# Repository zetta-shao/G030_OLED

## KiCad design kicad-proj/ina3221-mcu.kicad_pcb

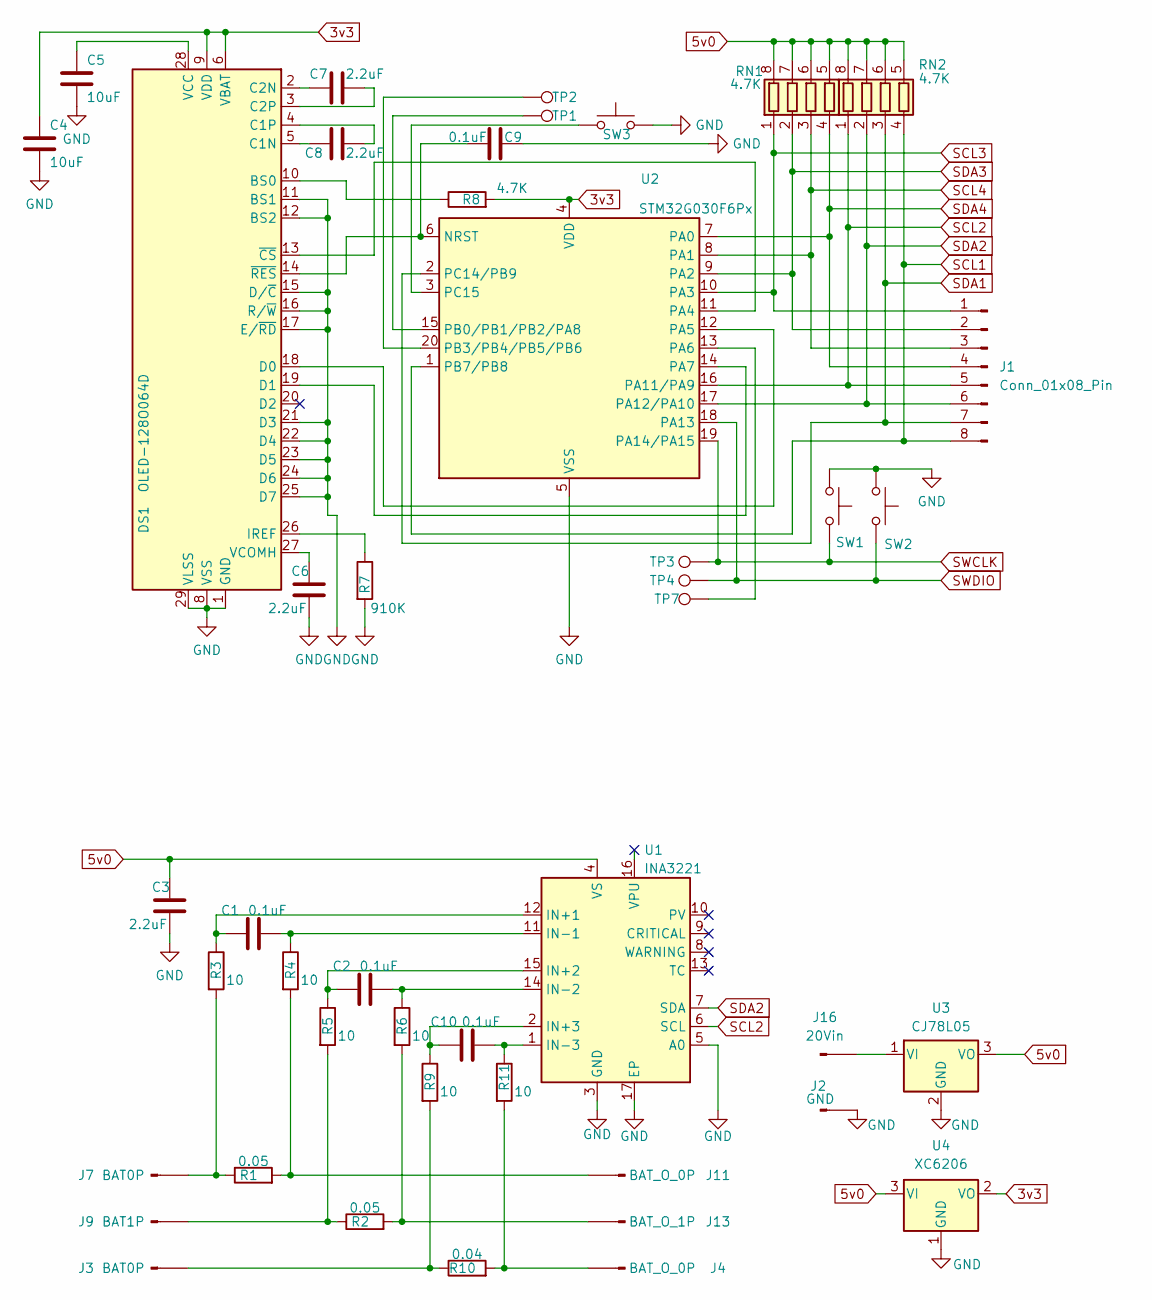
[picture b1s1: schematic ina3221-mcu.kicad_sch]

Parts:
C1, C2, C9, C10: 0.1uF; C_0603_1608Metric_Pad1.08x0.95mm_HandSolder
C3, C6, C7, C8: 2.2uF; C_0603_1608Metric_Pad1.08x0.95mm_HandSolder
C4, C5: 10uF; C_0603_1608Metric_Pad1.08x0.95mm_HandSolder
DS1: OLED-128O064D
J1: Conn_01x08_Pin; PinHeader_1x08_P1.00mm_Vertical
J2: GND; SolderWire-0.127sqmm_1x01_D0.48mm_OD1mm
J3, J7: BAT0P; SolderWire-0.127sqmm_1x01_D0.48mm_OD1mm
J4, J11: BAT_O_0P; SolderWire-0.127sqmm_1x01_D0.48mm_OD1mm
J9: BAT1P; SolderWire-0.127sqmm_1x01_D0.48mm_OD1mm
J13: BAT_O_1P; SolderWire-0.127sqmm_1x01_D0.48mm_OD1mm
J16: 20Vin; SolderWire-0.127sqmm_1x01_D0.48mm_OD1mm
R1, R2: 0.05; R_1206_3216Metric_Pad1.30x1.75mm_HandSolder
R3, R4, R5, R6, R9, R11: 10; R_0603_1608Metric_Pad0.98x0.95mm_HandSolder
R7: 910K; R_0603_1608Metric_Pad0.98x0.95mm_HandSolder
R8: 4.7K; R_0603_1608Metric_Pad0.98x0.95mm_HandSolder
R10: 0.04; R_1206_3216Metric_Pad1.30x1.75mm_HandSolder
RN1, RN2: 4.7K; R_Array_Concave_4x0603
SW1, SW2, SW3: SW_Push; SW_SPST_TL3305A
TP1, TP2: TestPoint; TestPoint_Pad_1.0x1.0mm
TP3: SWCLK; TestPoint_Pad_2.0x2.0mm
TP4: SWDIO; TestPoint_Pad_2.0x2.0mm
TP7: TestPoint_Pad_1.0x1.0mm
U1: INA3221; QFN-16-1EP_4x4mm_P0.65mm_EP2.1x2.1mm
U2: STM32G030F6Px; TSSOP-20_4.4x6.5mm_P0.65mm
U3: CJ78L05; SOT-89-3
U4: XC6206; SOT-23

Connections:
3v3: C4.1, DS1.6 (VBAT), DS1.9 (VDD), R8.2, U2.4 (VDD), U4.2 (VO)
5v0: C3.1, RN1.5 (R4.2), RN1.6 (R3.2), RN1.7 (R2.2), RN1.8 (R1.2), RN2.5 (R4.2), RN2.6 (R3.2), RN2.7 (R2.2), RN2.8 (R1.2), U1.4 (VS), U3.3 (VO), U4.3 (VI)
GND: C3.2, C4.2, C5.2, C6.2, C9.1, DS1.1 (GND), DS1.8 (VSS), DS1.11 (BS1), DS1.12 (BS2), DS1.15 (D/~C), DS1.16 (R/~W), DS1.17 (E/~RD), DS1.21 (D3), DS1.22 (D4), DS1.23 (D5), DS1.24 (D6), DS1.25 (D7), DS1.29 (VLSS), DS1.30 (GND), J2.1, R7.2, SW1.1, SW2.1, SW3.2, U1.3 (GND), U1.5 (A0), U1.17 (EP), U2.5 (VSS), U3.2 (GND), U4.1 (GND)
unnamed: DS1.10 (BS0), R8.1
unnamed: C8.1, DS1.5 (C1N)
unnamed: C8.2, DS1.4 (C1P)
unnamed: C7.1, DS1.2 (C2N)
unnamed: C7.2, DS1.3 (C2P)
unnamed: DS1.18 (D0), U2.12 (PA5)
unnamed: DS1.19 (D1), U2.14 (PA7)
unnamed: DS1.26 (IREF), R7.1
unnamed: C5.1, DS1.28 (VCC)
unnamed: C6.1, DS1.27 (VCOMH)
unnamed: DS1.13 (~CS), U2.11 (PA4)
unnamed: C9.2, DS1.14 (~RES), U2.6 (NRST)
unnamed: J3.1, R9.2, R10.1
unnamed: J4.1, R10.2, R11.2
unnamed: J7.1, R1.1, R3.2
unnamed: J9.1, R2.1, R5.2
unnamed: J11.1, R1.2, R4.2
unnamed: J13.1, R2.2, R6.2
unnamed: J16.1, U3.1 (VI)
unnamed: C1.1, R3.1, U1.12 (IN+1)
unnamed: C2.1, R5.1, U1.15 (IN+2)
unnamed: C10.1, R9.1, U1.2 (IN+3)
unnamed: C1.2, R4.1, U1.11 (IN-1)
unnamed: C2.2, R6.1, U1.14 (IN-2)
unnamed: C10.2, R11.1, U1.1 (IN-3)
unnamed: TP7.1, U2.13 (PA6)
unnamed: TP1.1, U2.15 (PB0/PB1/PB2/PA8)
unnamed: TP2.1, U2.20 (PB3/PB4/PB5/PB6)
unnamed: SW3.1, U2.3 (PC15)
SCL1: J1.8, RN2.4 (R4.1), U2.1 (PB7/PB8)
SCL2: J1.5, RN2.1 (R1.1), U1.6 (SCL), U2.16 (PA11/PA9)
SCL3: J1.1, RN1.1 (R1.1), U2.10 (PA3)
SCL4: J1.3, RN1.3 (R3.1), U2.8 (PA1)
SDA1: J1.7, RN2.3 (R3.1), U2.2 (PC14/PB9)
SDA2: J1.6, RN2.2 (R2.1), U1.7 (SDA), U2.17 (PA12/PA10)
SDA3: J1.2, RN1.2 (R2.1), U2.9 (PA2)
SDA4: J1.4, RN1.4 (R4.1), U2.7 (PA0)
SWCLK: SW1.2, TP3.1, U2.19 (PA14/PA15)
SWDIO: SW2.2, TP4.1, U2.18 (PA13)

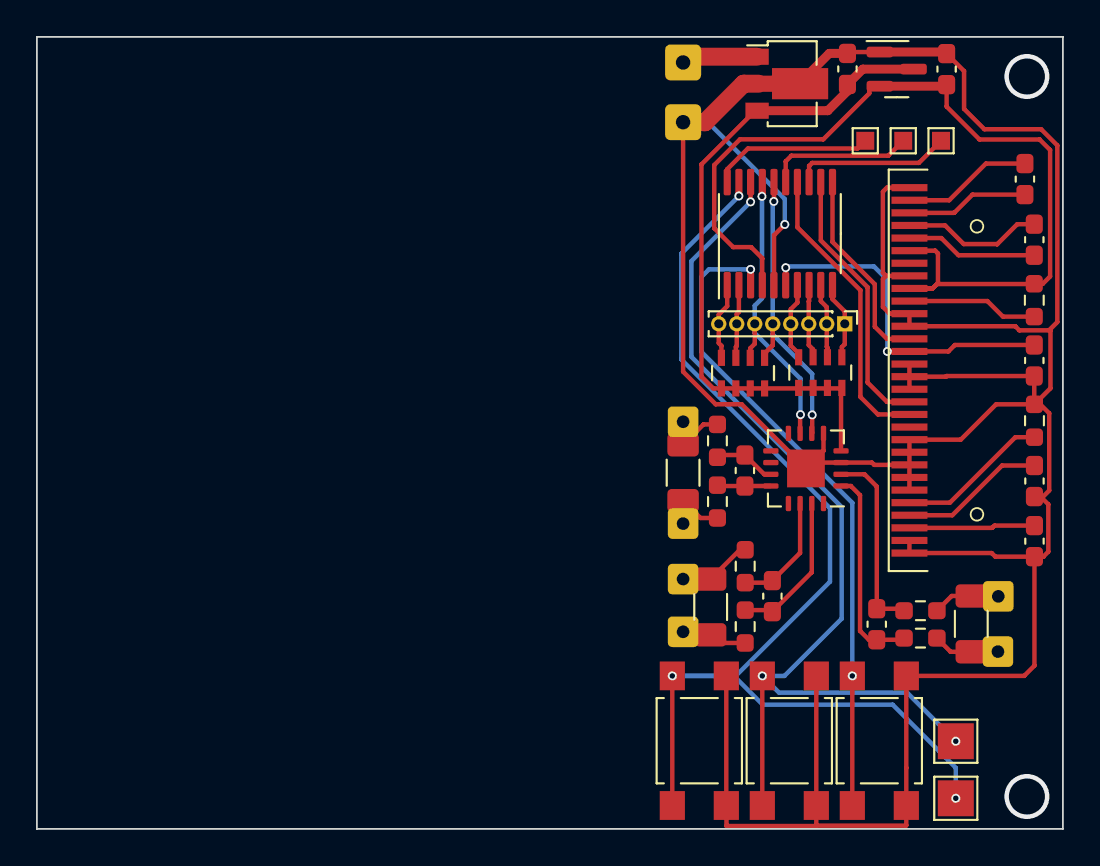
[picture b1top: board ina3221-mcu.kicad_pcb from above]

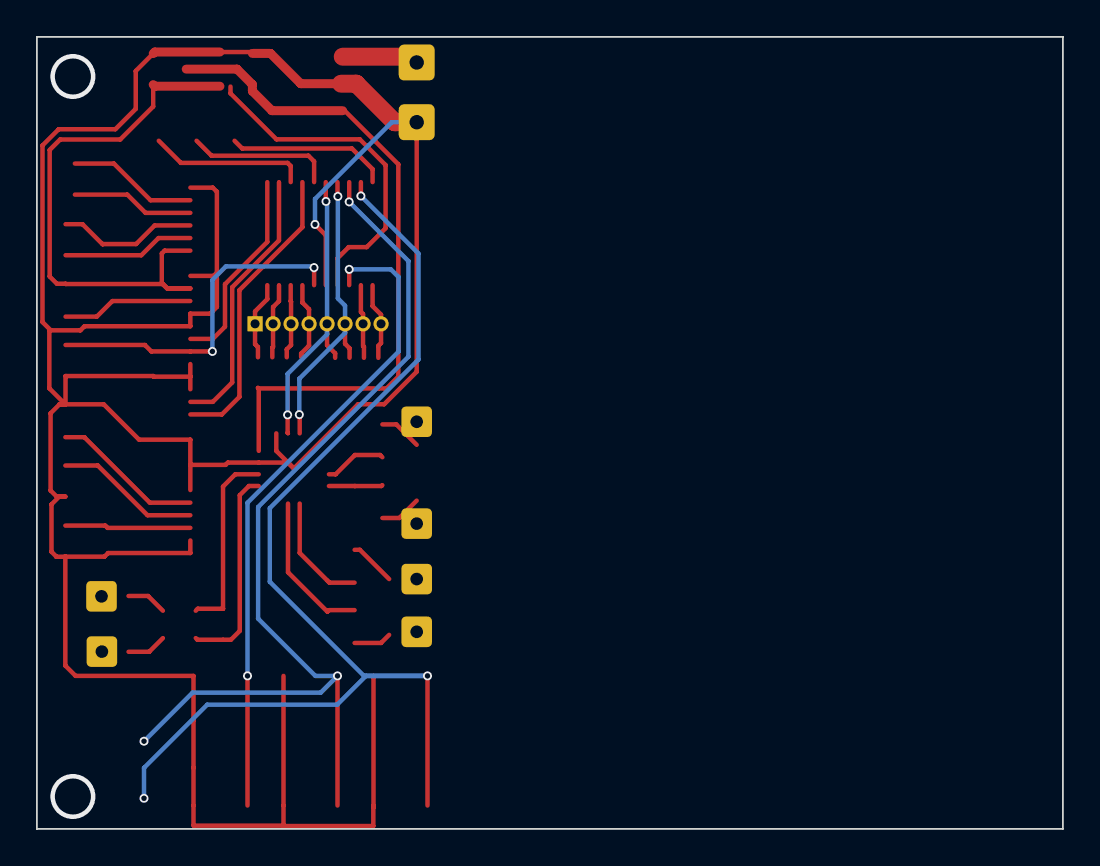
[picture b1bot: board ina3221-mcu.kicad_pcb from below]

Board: 2 copper layers, 57.0 x 44.0 mm, 45 parts (6 on the bottom side), 42 nets.

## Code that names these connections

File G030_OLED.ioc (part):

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Mcu.Name=STM32G030F6Px
Mcu.Package=TSSOP20
Mcu.UserName=STM32G030F6Px
PA0.Signal=GPIO_Input
PA1.GPIOParameters=GPIO_PuPd,GPIO_ModeDefaultOutputPP
PA1.GPIO_ModeDefaultOutputPP=GPIO_MODE_OUTPUT_OD
PA1.GPIO_PuPd=GPIO_NOPULL
PA1.Signal=GPIO_Output
PA11\ [PA9].Mode=I2C
PA11\ [PA9].Signal=I2C2_SCL
PA12\ [PA10].Mode=I2C
PA12\ [PA10].Signal=I2C2_SDA
PA13.GPIOParameters=GPIO_PuPd,GPIO_ModeDefaultEXTI
PA13.GPIO_ModeDefaultEXTI=GPIO_MODE_IT_RISING
PA13.GPIO_PuPd=GPIO_PULLUP
PA13.Signal=GPXTI13
PA14-BOOT0.GPIOParameters=GPIO_PuPd,GPIO_ModeDefaultEXTI
PA14-BOOT0.GPIO_ModeDefaultEXTI=GPIO_MODE_IT_RISING
PA14-BOOT0.GPIO_PuPd=GPIO_PULLUP
PA14-BOOT0.Signal=GPXTI14
PA14-BOOT0__PA15.StandardMode=true
PA2.Signal=GPIO_Input
PA3.GPIOParameters=GPIO_PuPd,GPIO_ModeDefaultOutputPP
PA3.GPIO_ModeDefaultOutputPP=GPIO_MODE_OUTPUT_OD
PA3.GPIO_PuPd=GPIO_NOPULL
PA3.Signal=GPIO_Output
PA4.Signal=GPIO_Output
PA5.Mode=TX_Only_Simplex_Unidirect_Master
PA5.Signal=SPI1_SCK
PA6.Signal=GPIO_Output
PA7.Mode=TX_Only_Simplex_Unidirect_Master
PA7.Signal=SPI1_MOSI
PA8.Signal=GPIO_Output
PB0__PB1__PB2__PA8.StandardMode=true
PB3.Signal=GPIO_Output
PB3__PB4__PB5__PB6.StandardMode=true
PB7__PB8.StandardMode=true
PB8.Mode=I2C
PB8.Signal=I2C1_SCL
PB9.Mode=I2C
PB9.Signal=I2C1_SDA
PC14-OSC32_IN\ (PC14)__PB9.StandardMode=true
PC15-OSC32_OUT\ (PC15).GPIOParameters=GPIO_PuPd,GPIO_ModeDefaultEXTI
PC15-OSC32_OUT\ (PC15).GPIO_ModeDefaultEXTI=GPIO_MODE_IT_RISING
PC15-OSC32_OUT\ (PC15).GPIO_PuPd=GPIO_PULLUP
PC15-OSC32_OUT\ (PC15).Signal=GPXTI15
RCC.HSE_VALUE=8000000
RCC.SYSCLKFreq_VALUE=16000000
board=custom

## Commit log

2024-03-27 STM32G030F6P6 battery/quickcharger project first release
2024-03-27 add ADCVref rename INA3221 i2c resource header calculate ADC vdda/vref value from adc vref read. add temperature adc read.
2024-03-28 change swi2c struct. add st7290, not test.
2024-03-28 fix lcd1602 timming issue.
2024-03-29 add st7290 (lcd12864) support
2024-03-29 test code for i2c ack
2024-04-01 software spi test code.
2024-04-03 codework for soft spi....
2024-04-03 fix soft spi bit mode, add cpol/cpha mode
2024-04-08 add gpio interrupt callback
2024-04-11 add 8bit fonts.
2024-04-11 add 8bit fonts support.
2024-10-12 just update code, no test
2025-03-16 add register define from document R003_v2.1
